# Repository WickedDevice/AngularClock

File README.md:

AngularClock
============

Factory Software for Angular Clock

Uses Libraries: 
* https://github.com/ichilton/mcp7941x_arduino
* https://github.com/PaulStoffregen/Time
* https://github.com/PaulStoffregen/Encoder

This is the software that comes loaded on Angular Clocks that come from Wicked Device.
* Details  @  http://shop.wickeddevice.com/angular-clock/ ‎
* Buy It @ http://shop.wickeddevice.com/product/angular-clock-kit/

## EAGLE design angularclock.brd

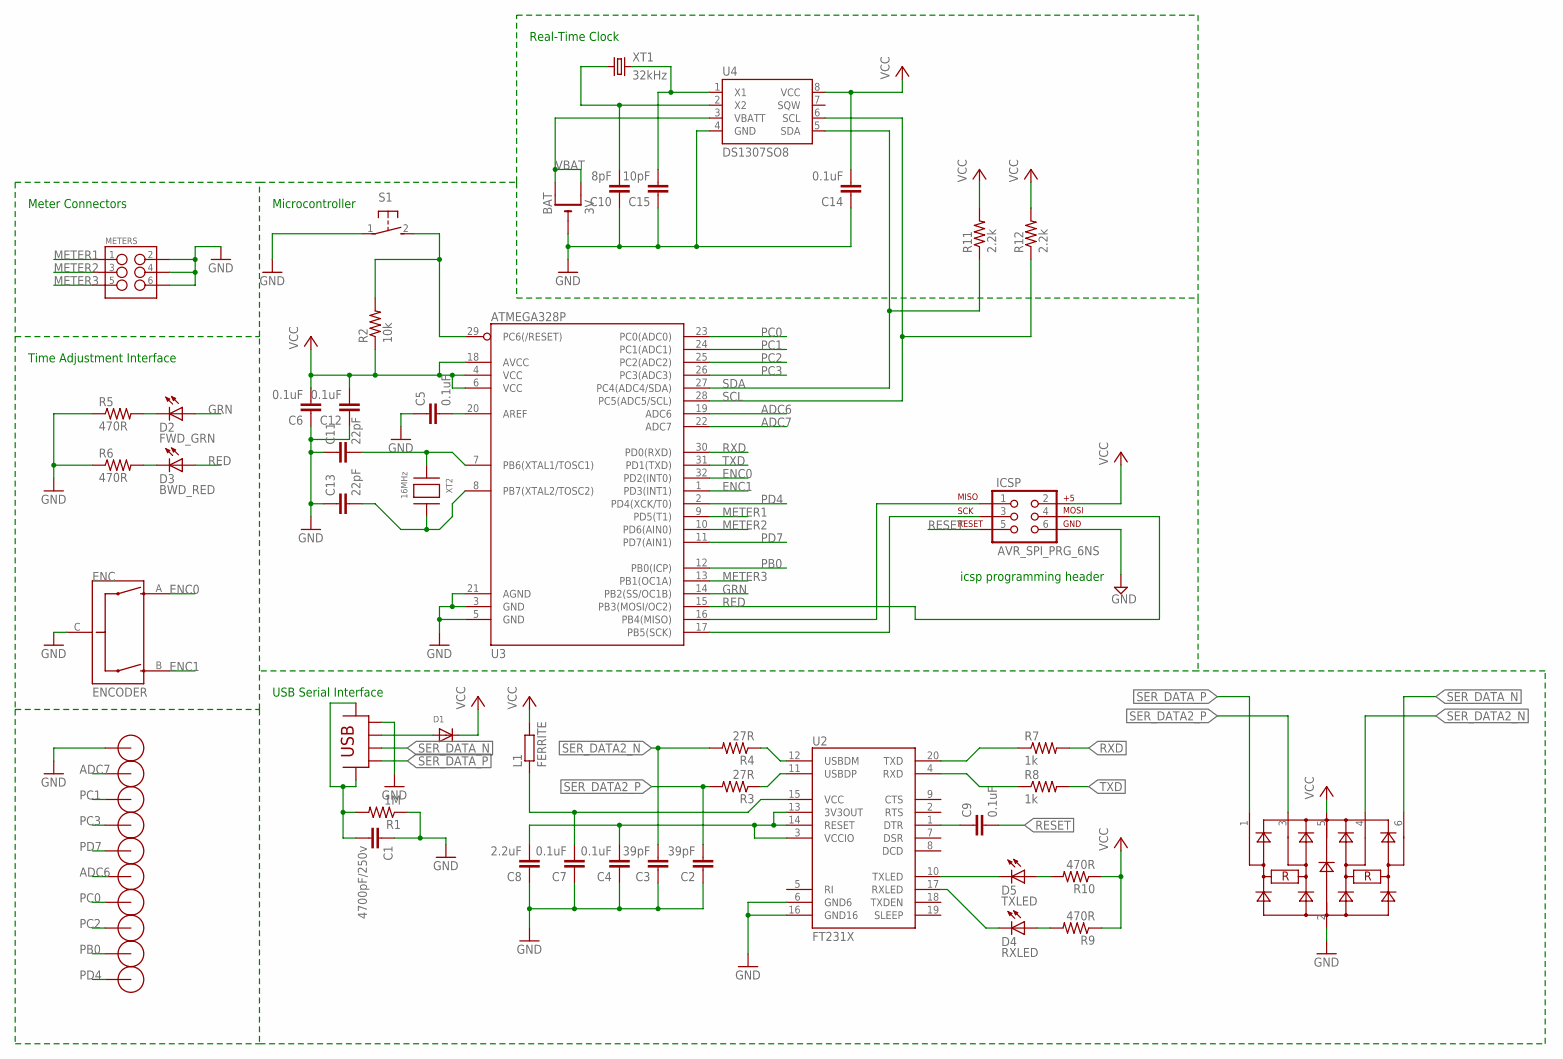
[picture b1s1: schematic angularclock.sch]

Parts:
BAT: 3V; CR1220-THM
C1: 4700pF/250v; 0805
C2, C3: 39pF; 0805
C4, C5, C6, C7, C9, C12, C14: 0.1uF; 0805
C8: 2.2uF; 0805
C10: 8pF; 0805
C11, C13: 22pF; 0805
C15: 10pF; 0805
D1: MBRM130LT1G; DO-216AA
D2: FWD_GRN; CHIPLED_0805
D3: BWD_RED; CHIPLED_0805
D4: RXLED; CHIPLED_0805
D5: TXLED; CHIPLED_0805
ENC: ENCODER; ENCODER-16MM-QUAD
ICSP: AVR_SPI_PRG_6NS; 2X3-NS
L1: FERRITE; R0805
METERS: M03X2NO_SILK; 2X3-NS
R1: 1M; 0805
R2: 10k; 0805
R3, R4: 27R; 0805
R5, R6, R9, R10: 470R; 0805
R7, R8: 1k; 0805
R11, R12: 2.2k; 0805
S1: 31-XX; B3F-31XX
U1: IP4234CZ6; SOT457
U2: FT231X; SSOP20
U3: ATMEGA328P; TQFP32-08
U4: DS1307SO8; SO08
U$1, U$2, U$3, U$4, U$5, U$6, U$7, U$8, U$9, U$10: 1PIN
USB: MICRO-USB-POWERMICRO-USB-2-ROUND-HOLES; WICKED-DEVICE_MICRO-USB-4
XT1: 32kHz; CRYSTAL_TC26V
XT2: 16MHz; ABLS

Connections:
ADC6: U3.19 (ADC6), U$1.1
ADC7: U3.22 (ADC7), U$4.1
ENC0: ENC.A, U3.32 (PD2(INT0))
ENC1: ENC.B, U3.1 (PD3(INT1))
FT33: C4.2, C8.2, U2.3 (VCCIO), U2.13 (3V3OUT), U2.14 (RESET)
FTDI_VCC: C7.2, L1.1, U2.15 (VCC)
GND: BAT.-, C1.1, C2.1, C3.1, C4.1, C5.1, C6.1, C7.1, C8.1, C10.1, C11.1, C12.1, C13.1, C14.1, C15.1, ENC.C, ICSP.6, METERS.2, METERS.4, METERS.6, R1.1, R5.1, R6.1, S1.1, U1.2, U2.6 (GND6), U2.16 (GND16), U3.3 (GND), U3.5 (GND), U3.21 (AGND), U4.4 (GND), U$2.1, USB.GND
GRN: D2.A, U3.14 (PB2(SS/OC1B))
METER1: METERS.1, U3.9 (PD5(T1))
METER2: METERS.3, U3.10 (PD6(AIN0))
METER3: METERS.5, U3.13 (PB1(OC1A))
MISO: ICSP.1, U3.16 (PB4(MISO))
unnamed: C11.2, U3.7 (PB6(XTAL1/TOSC1)), XT2.1
unnamed: C5.2, U3.20 (AREF)
unnamed: D2.C, R5.2
unnamed: C13.2, U3.8 (PB7(XTAL2/TOSC2)), XT2.2
unnamed: D3.C, R6.2
unnamed: R7.1, U2.20 (TXD)
unnamed: C1.2, R1.2, USB.P$2, USB.P$3
unnamed: C15.2, U4.1 (X1), XT1.2
unnamed: C10.2, U4.2 (X2), XT1.1
unnamed: R8.1, U2.4 (RXD)
unnamed: D5.C, U2.10 (TXLED)
unnamed: D4.C, U2.17 (RXLED)
unnamed: D5.A, R10.2
unnamed: D4.A, R9.2
unnamed: C9.1, U2.1 (DTR)
PB0: U3.12 (PB0(ICP)), U$5.1
PC0: U3.23 (PC0(ADC0)), U$3.1
PC1: U3.24 (PC1(ADC1)), U$6.1
PC2: U3.25 (PC2(ADC2)), U$7.1
PC3: U3.26 (PC3(ADC3)), U$10.1
PD4: U3.2 (PD4(XCK/T0)), U$9.1
PD7: U3.11 (PD7(AIN1)), U$8.1
RED: D3.A, ICSP.4, U3.15 (PB3(MOSI/OC2))
RESET: C9.2, ICSP.5, R2.2, S1.2 (S), U3.29 (PC6(/RESET))
RXD: R7.2, U3.30 (PD0(RXD))
SCK: ICSP.3, U3.17 (PB5(SCK))
SCL: R12.1, U3.28 (PC5(ADC5/SCL)), U4.6 (SCL)
SDA: R11.1, U3.27 (PC4(ADC4/SDA)), U4.5 (SDA)
SER_DATA2_N: C3.2, R4.2, U1.4 (6)
SER_DATA2_P: C2.2, R3.2, U1.3
SER_DATA_N: U1.6 (4), USB.D-
SER_DATA_P: U1.1, USB.D+
TXD: R8.2, U3.31 (PD1(TXD))
USB_N: R4.1, U2.12 (USBDM)
USB_P: R3.1, U2.11 (USBDP)
USB_VCC: D1.+, USB.VBUS
VBAT: BAT.+1 (+), BAT.+2 (+1), U4.3 (VBATT)
VCC: C6.2, C12.2, C14.2, D1.-, ICSP.2, L1.2, R2.1, R9.1, R10.1, R11.2, R12.2, U1.5, U3.4 (VCC), U3.6 (VCC), U3.18 (AVCC), U4.8 (VCC)

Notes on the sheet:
icsp programming header
USB Serial Interface
Microcontroller
Meter Connectors
Time Adjustment Interface
Real-Time Clock

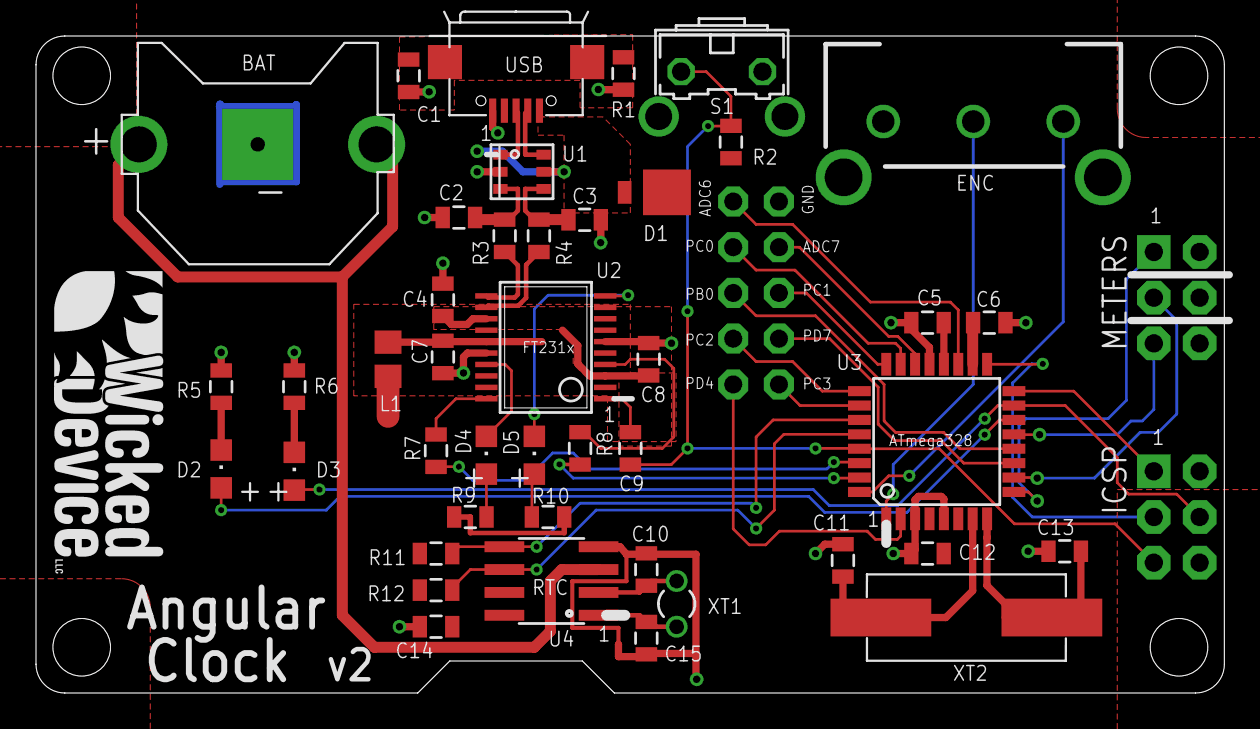
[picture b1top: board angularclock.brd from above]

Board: 2 copper layers, 66.0 x 36.5 mm, 56 parts (0 on the bottom side), 50 nets.

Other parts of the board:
U$11: WICKEDLOGOTYPE

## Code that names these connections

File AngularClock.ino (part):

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
Encoder myEnc(ENCA,ENCB);

// Map Meters to Arduino Pins Meter1 is on the left of clock
#define METER1 9 //purple wire
#define METER2 6 //blue wire
#define METER3 5 //orange wire

// Associate METER1, METER2, METER3 with output functions -- SECONDS,MINUTES,HOURS,TEMPERATURE,HOURS2,HOURS3 
// (HOURS2,HOURS2 are for multitimezone clock)
#define HOURS METER1
#define MINUTES METER2
#define SECONDS METER3

#define TOTAL_METERS 10
#define MIN_ANALOG 0
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
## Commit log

2014-03-17 added sketch
2014-03-19 Add Meter Clock Faces
2014-09-03 added eagle files and schematic pdf
2015-09-23 addressing minutes overflow issues related to calibration

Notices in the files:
AngularClock.ino:
MIT license, all text above must be included in any redistribution
parts and their libraries:
SparkFun-DigitalIC: Licensing: CC v3.0 Share-Alike You are welcome to use this library for commercial purposes.
